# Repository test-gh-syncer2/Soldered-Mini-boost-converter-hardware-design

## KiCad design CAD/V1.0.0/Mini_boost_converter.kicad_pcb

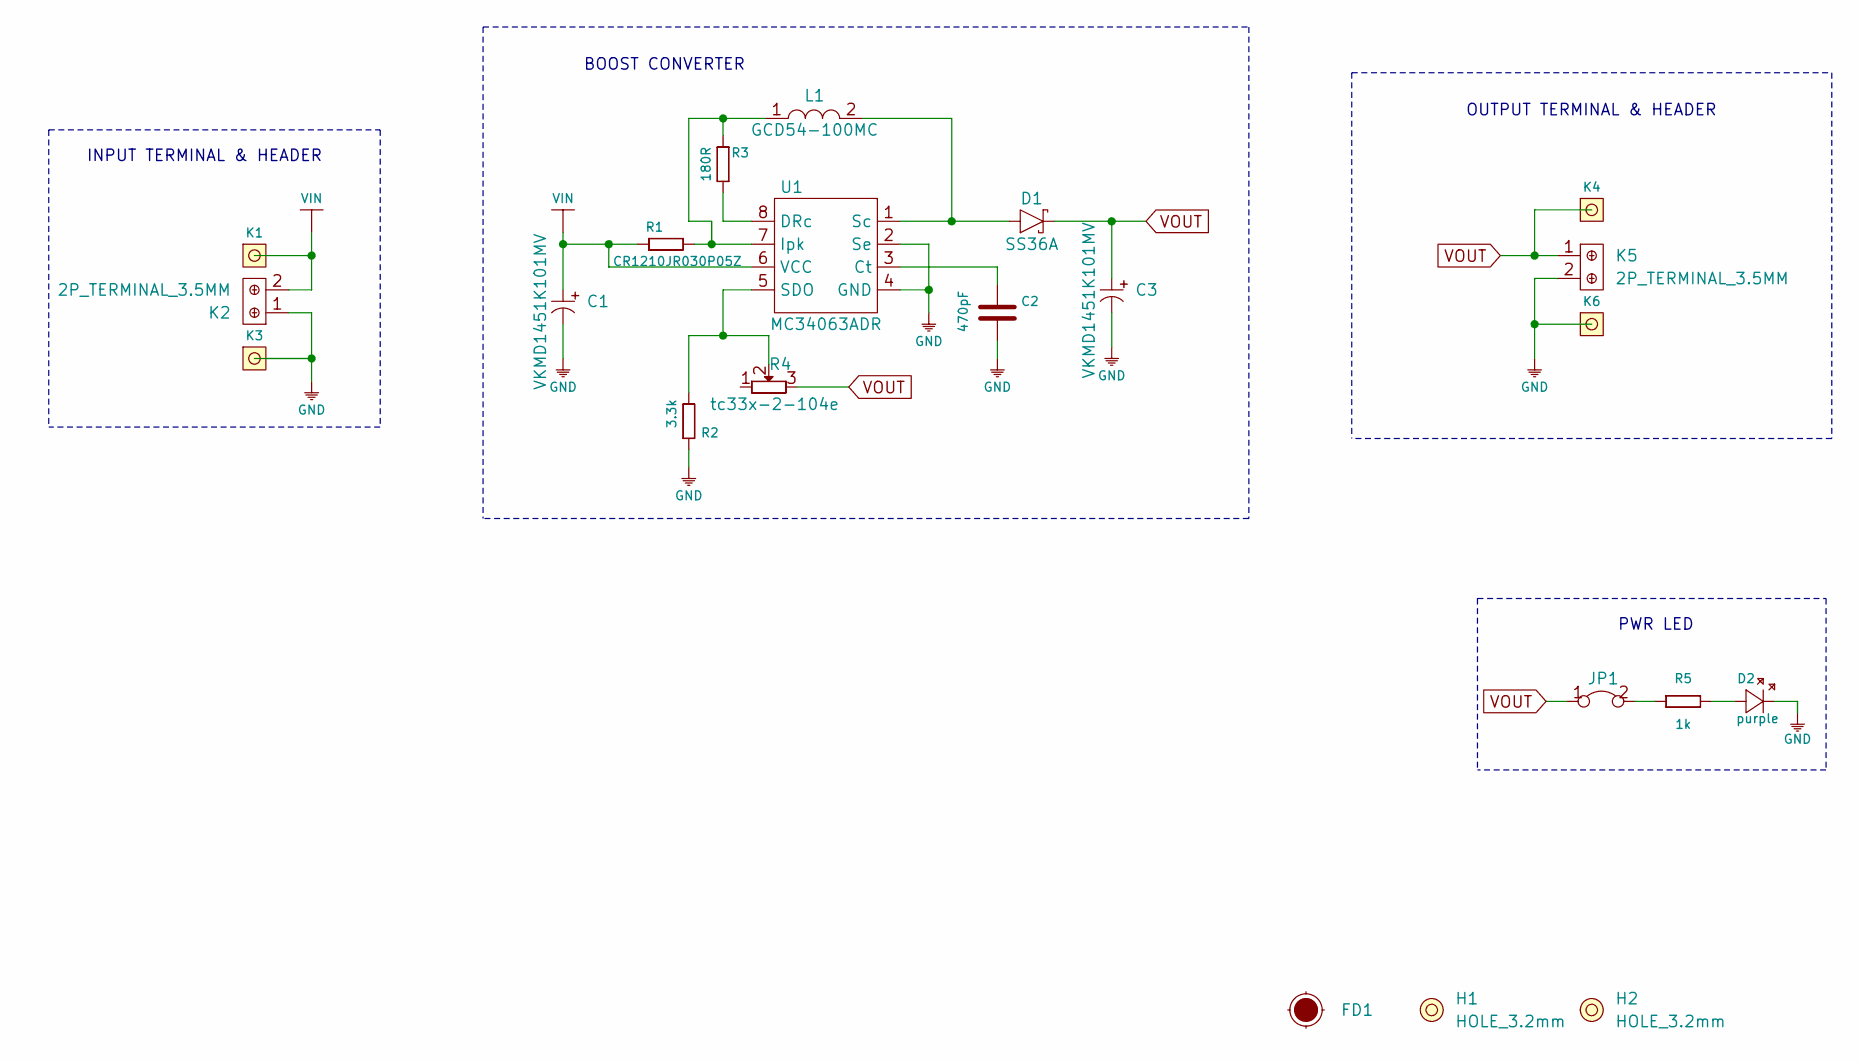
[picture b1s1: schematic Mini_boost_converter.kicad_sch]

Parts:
C1, C3: VKMD1451K101MV; ELECTROLITIC_CAP_8x8x14.5
C2: 470pF; 0603C
D1: SS36A; SMA_DIODE
D2: purple; 0402LED
FD1: Fiducial_Stencil; FIDUCIAL_1MM_PASTE
H1, H2: HOLE_3.2mm
JP1: SMD-JUMPER-CONNECTED_TRACE_NOSLODERMASK
K1, K3, K4, K6: HEADER_MALE_1X1
K2, K5: 2P_TERMINAL_3.5MM
L1: GCD54-100MC; CMLF0504-330KTT
R1: CR1210JR030P05Z; 1210R
R2: 3.3k; 0603R
R3: 180R; 0603R
R4: tc33x-2-104e; tc33x-2-103e
R5: 1k; 0402R
U1: MC34063ADR; SOIC−8

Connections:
GND: C1.2 (-), C2.1, C3.2 (-), D2.2 (K), K2.1, K3.1, K5.2, K6.1, R2.1, U1.2 (Se), U1.4 (GND)
unnamed: C2.2, U1.3 (Ct)
unnamed: D1.1 (A), L1.2, U1.1 (Sc)
unnamed: D2.1 (A), R5.2
unnamed: JP1.2, R5.1
unnamed: L1.1, R1.2, R3.1, U1.7 (Ipk)
unnamed: R2.2, R4.2, U1.5 (SDO)
unnamed: R3.2, U1.8 (DRc)
VIN: C1.1 (+), K1.1, K2.2, R1.1, U1.6 (VCC)
VOUT: C3.1 (+), D1.2 (C), JP1.1, K4.1, K5.1, R4.3

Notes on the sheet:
INPUT TERMINAL & HEADER
BOOST CONVERTER
PWR LED
OUTPUT TERMINAL & HEADER

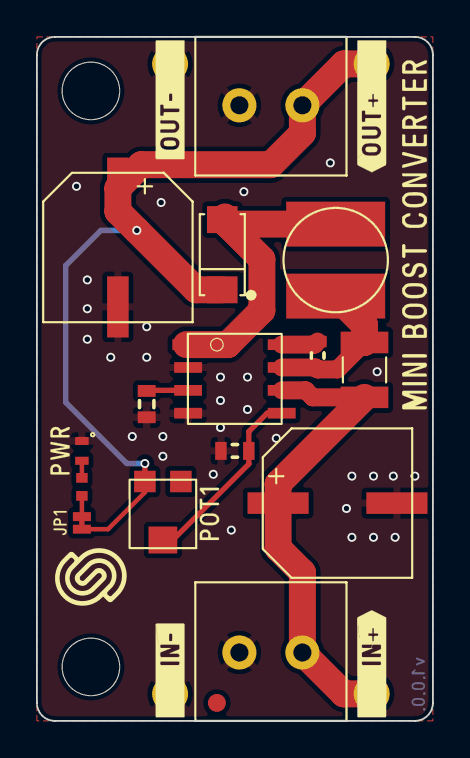
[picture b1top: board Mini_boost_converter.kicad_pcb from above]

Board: 2 copper layers, 22.0 x 38.0 mm, 22 parts (0 on the bottom side), 10 nets.

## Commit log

2021-09-23 Syncing to git
2021-09-23 Updating open source files.
